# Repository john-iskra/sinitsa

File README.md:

## Sinitsa PCB Layout

Very broadband receiver, designed to pick up any radio signal in the immediate area. Useful for finding sources of interference.

Improved version of the ["Sinitsa" modification to the Amazing Allband Receiver](http://techlib.com/electronics/sinitsa.htm#Sinitsa).

This represents the diode detector section of the [original Sinitsa](https://cryptomuseum.com/df/sinitsa/index.htm). Adding filters and pre-amplifiers is left to the user.

### Ordering

Download the Gerber files from the `gerbers/` directory. Send them to your PCB manufacturer of choice.

### Parts list and assembly

The following parts need to be populated onto the board.

Once the board is populated and tested:

1. Cover the RF input section with some non-conducting tape. Then put copper or aluminum foil over top. Connect the foil to ground. This will shield the quite sensitive input section from unwanted signals in the area (cell phones, etc).
2. Use epoxy to secure the potentiometers against physical shocks. Their pins are fairly fragile.
3. Cover the whole board in heat shrink tubing. Transparent heat shrink is recommended so the power LED is visible.

|Ref                           |Qnty|Value          |Cmp name                             |Footprint                                                   |Description                                                                                           |Vendor|
|------------------------------|----|---------------|-------------------------------------|------------------------------------------------------------|------------------------------------------------------------------------------------------------------|------|
|BAT1,                         |1   |Battery Clip   |Conn_01x02                           |Connector_PinHeader_2.54mm:PinHeader_1x02_P2.54mm_Vertical  | 9V battery clip|      |
|C1,                           |1   |100pF          |C                                    |Capacitor_SMD:C_0402_1005Metric                             |Unpolarized capacitor                                                                                 |      |
|C2, C4, C5, C8, C9, C10, C11, |7   |1nF            |C                                    |Capacitor_SMD:C_0402_1005Metric                             |Unpolarized capacitor                                                                                 |      |
|C3, C12, C100,                |3   |100nF          |C                                    |Capacitor_SMD:C_0402_1005Metric                             |Unpolarized capacitor                                                                                 |      |
|C6,                           |1   |47nF           |C                                    |Capacitor_SMD:C_0603_1608Metric                             |Unpolarized capacitor                                                                                 |      |
|C7,                           |1   |220uF          |C_Polarized-Device-sinitsa-rescue    |Capacitor_SMD:CP_Elec_6.3x7.7                               |                                                                                                      |      |
|C13,                          |1   |1uF            |C                                    |Capacitor_SMD:C_0402_1005Metric                             |Unpolarized capacitor                                                                                 |      |
|D1,                           |1   |BAT17          |D_Schottky                           |Diode_SMD:D_SOT-23_ANK                                      |Schottky diode                                                                                        |      |
|D2, D3, D4,                   |3   |1N914WT        |1N914WT                              |Diode_SMD:D_SOD-523                                         |75V 0.15A Fast switching Diode, SOD-523                                                               |      |
|IC1,                          |1   |LM358          |LM358                                |Package_SO:SOIC-8_3.9x4.9mm_P1.27mm                         |Low-Power, Dual Operational Amplifiers, DIP-8/SOIC-8/TO-99-8                                          |      |
|J2,                           |1   |KLBR_4         |KLBR_4-LUMBERG_3.5-sinitsa-rescue    |Lumberg_3.5:Lumberg-KLBR_4-0                                |                                                                                                      |      |
|L1,                           |1   |10uH           |L                                    |Inductor_SMD:L_0805_2012Metric                              |Inductor                                                                                              |      |
|L2,                           |1   |39n            |L                                    |Inductor_SMD:L_0402_1005Metric                              |Inductor                                                                                              |      |
|LED1,                         |1   |RED LED        |LED                                  |LED_SMD:LED_0805_2012Metric                                 |Light emitting diode                                                                                  |      |
|R1, R8,                       |2   |10K            |R                                    |Resistor_SMD:R_0402_1005Metric                              |Resistor                                                                                              |      |
|R2, R3,                       |2   |10M            |R                                    |Resistor_SMD:R_0402_1005Metric                              |Resistor                                                                                              |      |
|R4, R11, R12, R19,            |4   |100K           |R                                    |Resistor_SMD:R_0402_1005Metric                              |Resistor                                                                                              |      |
|R5,                           |1   |100            |R                                    |Resistor_SMD:R_0402_1005Metric                              |Resistor                                                                                              |      |
|R6, R9, R22,                  |3   |220K           |R                                    |Resistor_SMD:R_0402_1005Metric                              |Resistor                                                                                              |      |
|R7,                           |1   |10             |R                                    |Resistor_SMD:R_0402_1005Metric                              |Resistor                                                                                              |      |
|R10,                          |1   |3k3            |R                                    |Resistor_SMD:R_0402_1005Metric                              |Resistor                                                                                              |      |
|R13,                          |1   |200K           |R                                    |Resistor_SMD:R_0402_1005Metric                              |Resistor                                                                                              |      |
|R14,                          |1   |470K           |R                                    |Resistor_SMD:R_0402_1005Metric                              |Resistor                                                                                              |      |
|R15, R16, R17, R21,           |4   |5.1K           |R                                    |Resistor_SMD:R_0402_1005Metric                              |Resistor                                                                                              |      |
|R18,                          |1   |10K            |R_Potentiometer-Device-sinitsa-rescue|Potentiometer_THT:Potentiometer_Alps_RK097_Single_Horizontal|                                                                                                      |      |
|R20,                          |1   |100K           |R_Potentiometer-Device-sinitsa-rescue|Potentiometer_THT:Potentiometer_Alps_RK097_Single_Horizontal|                                                                                                      |      |
|T1,                           |1   |MMST2222A-7-F  |BC847W                               |Package_TO_SOT_SMD:SOT-323_SC-70                            |0.1A Ic, 45V Vce, NPN Transistor, SOT-323                                                             |      |
|X1,                           |1   |AMPHENOL 132289|Conn_Coaxial                         |Connector_Coaxial:SMA_Amphenol_132289_EdgeMount             |coaxial connector                                                 |      |

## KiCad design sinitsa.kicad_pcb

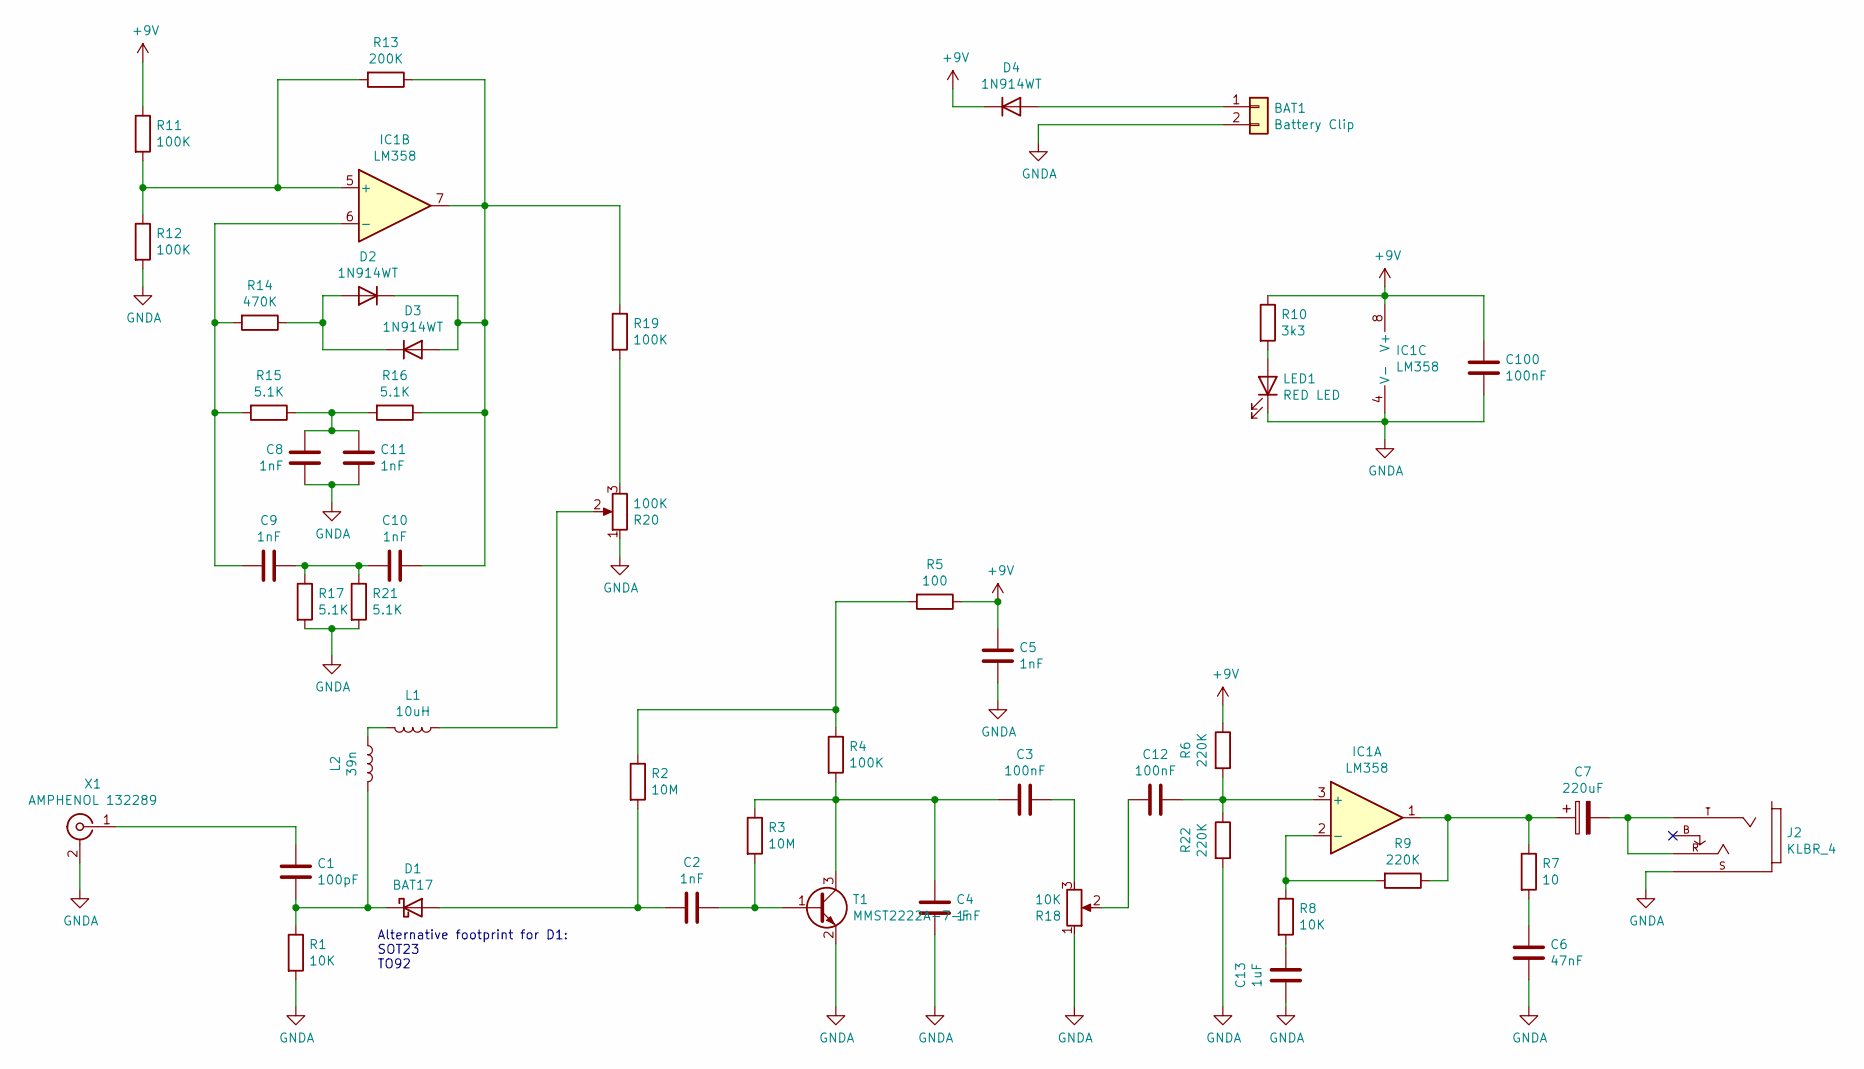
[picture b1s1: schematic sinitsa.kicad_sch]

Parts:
BAT1: Battery Clip; PinHeader_1x02_P2.54mm_Vertical
C1: 100pF; C_0402_1005Metric
C2, C4, C5, C8, C9, C10, C11: 1nF; C_0402_1005Metric
C3, C12, C100: 100nF; C_0402_1005Metric
C6: 47nF; C_0603_1608Metric
C7: 220uF; CP_Elec_6.3x7.7
C13: 1uF; C_0402_1005Metric
D1: BAT17; D_SOT-23_ANK
D2, D3, D4: 1N914WT; D_SOD-523
IC1: LM358; SOIC-8_3.9x4.9mm_P1.27mm
J2: KLBR_4; Lumberg-KLBR_4-0
L1: 10uH; L_0805_2012Metric
L2: 39n; L_0402_1005Metric
LED1: RED LED; LED_0805_2012Metric
R1, R8: 10K; R_0402_1005Metric
R2, R3: 10M; R_0402_1005Metric
R4, R11, R12, R19: 100K; R_0402_1005Metric
R5: 100; R_0402_1005Metric
R6, R9, R22: 220K; R_0402_1005Metric
R7: 10; R_0402_1005Metric
R10: 3k3; R_0402_1005Metric
R13: 200K; R_0402_1005Metric
R14: 470K; R_0402_1005Metric
R15, R16, R17, R21: 5.1K; R_0402_1005Metric
R18: 10K; Potentiometer_Alps_RK097_Single_Horizontal
R20: 100K; Potentiometer_Alps_RK097_Single_Horizontal
T1: MMST2222A-7-F; SOT-323_SC-70
X1: AMPHENOL 132289; SMA_Amphenol_132289_EdgeMount

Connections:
+9V: C5.1, C100.1, D4.1 (K), IC1.8 (V+), R5.1, R6.1, R10.1, R11.1
GNDA: BAT1.2, C4.2, C5.2, C6.2, C8.1, C11.2, C13.2, C100.2, IC1.4 (V-), J2.S, LED1.1 (K), R1.2, R12.2, R17.2, R18.1, R20.1, R21.2, R22.2, T1.2 (E), X1.2 (Ext)
unnamed: BAT1.1, D4.2 (A)
unnamed: C1.1, X1.1 (In)
unnamed: C1.2, D1.1 (K), L2.2, R1.1
unnamed: C2.1, R3.2, T1.1 (B)
unnamed: C2.2, D1.2 (A), R2.2
unnamed: C3.1, R18.3
unnamed: C3.2, C4.1, R3.1, R4.2, T1.3 (C)
unnamed: C6.1, R7.2
unnamed: C7.1, IC1.1, R7.1, R9.1
unnamed: C7.2, J2.R, J2.T
unnamed: C9.2, IC1.6 (-), R14.2, R15.2
unnamed: C10.1, D2.1 (K), D3.2 (A), IC1.7, R13.1, R16.1, R19.1
unnamed: C9.1, C10.2, R17.1, R21.1
unnamed: C8.2, C11.1, R15.1, R16.2
unnamed: D2.2 (A), D3.1 (K), R14.1
unnamed: IC1.2 (-), R8.1, R9.2
unnamed: C12.1, IC1.3 (+), R6.2, R22.1
unnamed: IC1.5 (+), R11.2, R12.1, R13.2
unnamed: L1.1, R20.2
unnamed: L1.2, L2.1
unnamed: LED1.2 (A), R10.2
unnamed: R2.1, R4.1, R5.2
unnamed: C13.1, R8.2
unnamed: C12.2, R18.2
unnamed: R19.2, R20.3

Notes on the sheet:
Alternative footprint for D1: SOT23 TO92

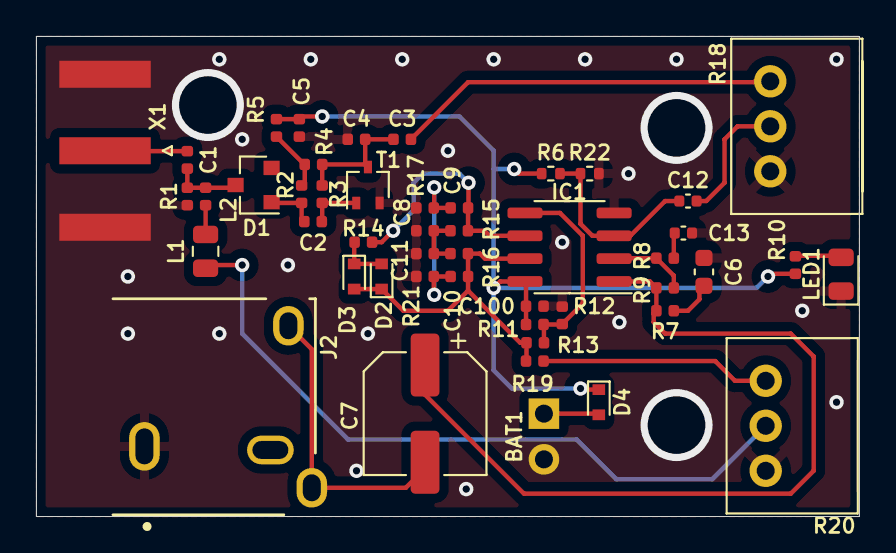
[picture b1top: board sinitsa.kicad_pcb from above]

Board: 2 copper layers, 45.7 x 26.7 mm, 48 parts (0 on the bottom side), 27 nets.

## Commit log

2021-02-04 initial
